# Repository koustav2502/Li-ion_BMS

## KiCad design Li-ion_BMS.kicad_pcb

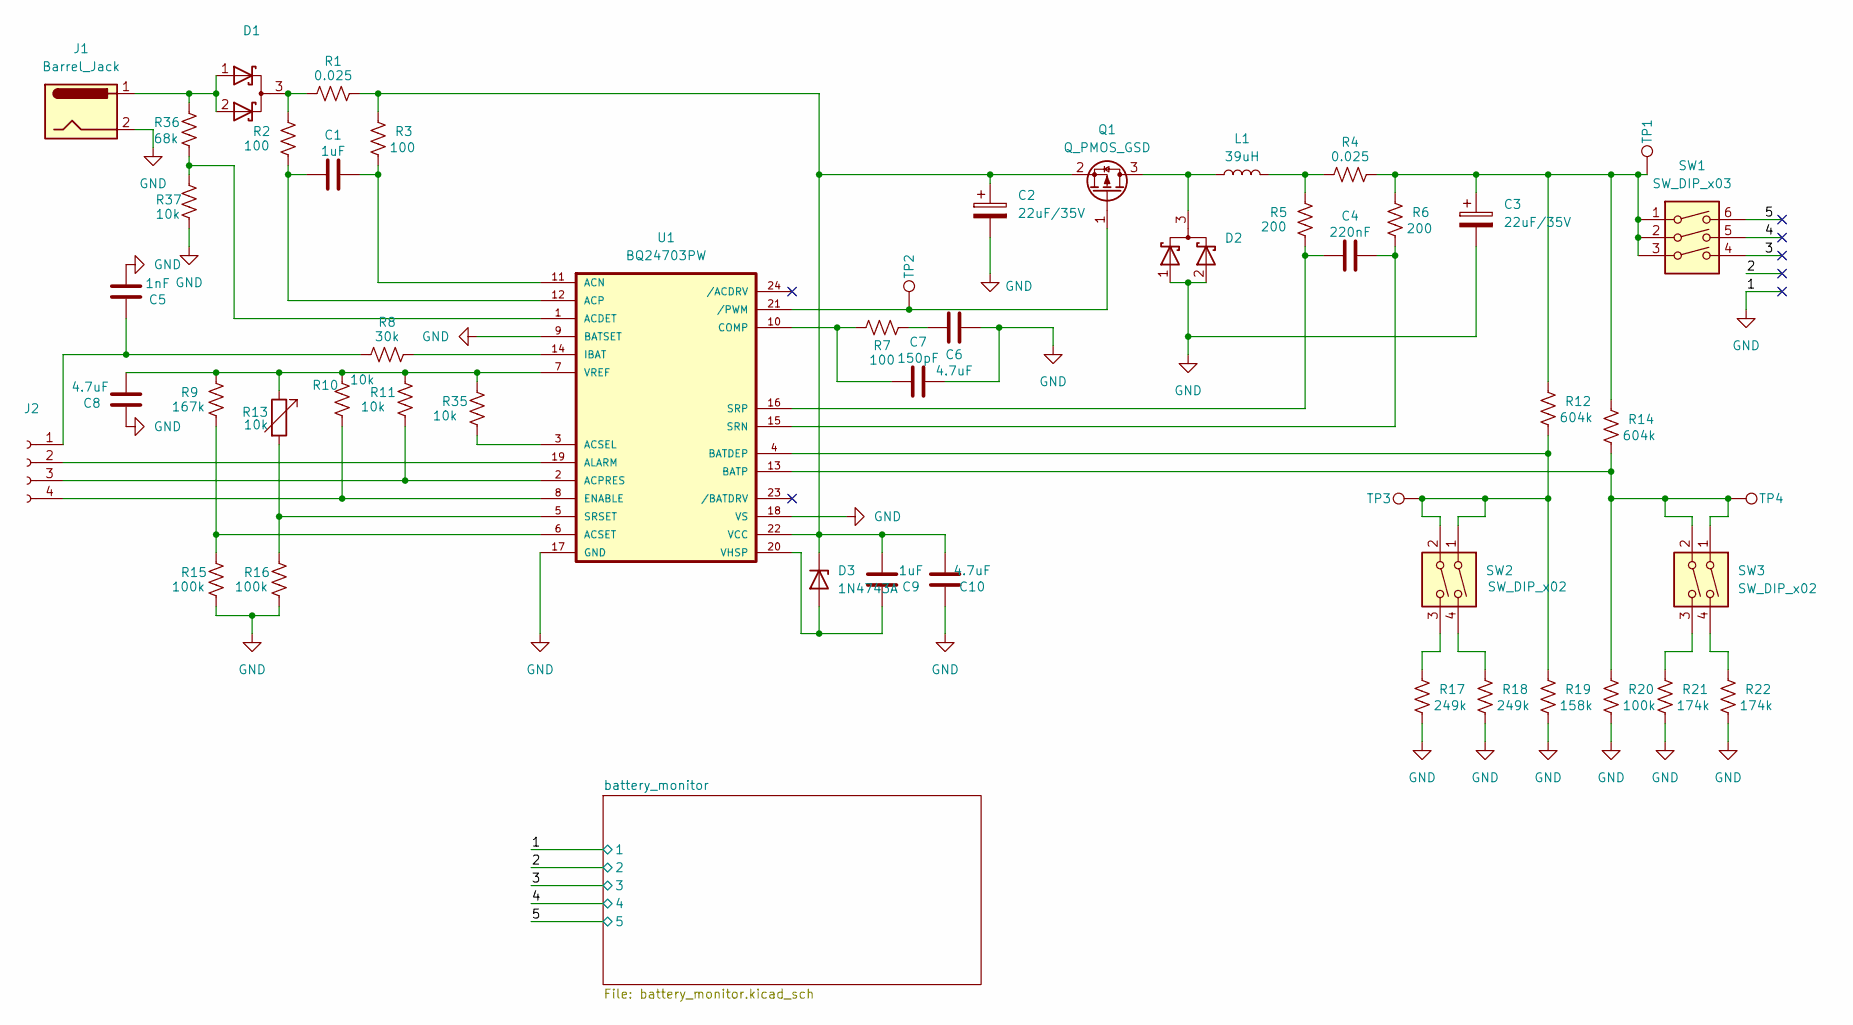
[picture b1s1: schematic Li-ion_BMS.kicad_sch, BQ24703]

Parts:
C1, C9: 1uF; C_Disc_D5.0mm_W2.5mm_P5.00mm
C2, C3: 22uF/35V; CP_Radial_D6.3mm_P2.50mm
C4: 220nF; C_Disc_D5.0mm_W2.5mm_P5.00mm
C5: 1nF; C_Disc_D3.0mm_W1.6mm_P2.50mm
C6, C8, C10: 4.7uF; C_Disc_D5.0mm_W2.5mm_P5.00mm
C7: 150pF; C_Disc_D3.0mm_W1.6mm_P2.50mm
D1, D2: DualSchottkyCommC; TO-220-3_Vertical
D3: 1N4743A; D_DO-41_SOD81_P10.16mm_Horizontal
J1: Barrel_Jack; BarrelJack_Horizontal
J2: Conn_01x04_Socket; PinHeader_1x05_P2.54mm_Vertical
L1: 39uH; L_Radial_D12.0mm_P10.00mm_Neosid_SD12k_style1
Q1: Q_PMOS_GSD; TO-220-3_Vertical
R1, R4: 0.025; R_Axial_DIN0411_L9.9mm_D3.6mm_P15.24mm_Horizontal
R2, R3, R7: 100; R_Axial_DIN0207_L6.3mm_D2.5mm_P10.16mm_Horizontal
R5, R6: 200; R_Axial_DIN0207_L6.3mm_D2.5mm_P10.16mm_Horizontal
R8: 30k; R_Axial_DIN0207_L6.3mm_D2.5mm_P10.16mm_Horizontal
R9: 167k; R_Axial_DIN0207_L6.3mm_D2.5mm_P10.16mm_Horizontal
R10, R11, R35, R37: 10k; R_Axial_DIN0207_L6.3mm_D2.5mm_P10.16mm_Horizontal
R12, R14: 604k; R_Axial_DIN0207_L6.3mm_D2.5mm_P10.16mm_Horizontal
R13: 10k; Potentiometer_Bourns_3296W_Vertical
R15, R16, R20: 100k; R_Axial_DIN0207_L6.3mm_D2.5mm_P10.16mm_Horizontal
R17, R18: 249k; R_Axial_DIN0207_L6.3mm_D2.5mm_P10.16mm_Horizontal
R19: 158k; R_Axial_DIN0207_L6.3mm_D2.5mm_P10.16mm_Horizontal
R21, R22: 174k; R_Axial_DIN0207_L6.3mm_D2.5mm_P10.16mm_Horizontal
R36: 68k; R_Axial_DIN0207_L6.3mm_D2.5mm_P10.16mm_Horizontal
SW1: SW_DIP_x03; SW_DIP_SPSTx03_Slide_9.78x9.8mm_W8.61mm_P2.54mm
SW2, SW3: SW_DIP_x02; SW_DIP_SPSTx02_Slide_9.78x7.26mm_W8.61mm_P2.54mm
TP1, TP2, TP3, TP4: TestPoint; TestPoint_THTPad_D2.0mm_Drill1.0mm
U1: BQ24703PW; TSSOP-24_4.4x7.8mm_P0.65mm

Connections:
/3: SW1.4; also elsewhere on the board
/4: SW1.5; also elsewhere on the board
/5: SW1.6; also elsewhere on the board
GND: C2.2, C3.2, C5.1, C6.2, C7.2, C8.2, C10.2, D2.1 (A), D2.2 (A), J1.2, R15.2, R16.2, R17.2, R18.2, R19.2, R20.2, R21.2, R22.2, R37.2, U1.9 (BATSET), U1.17 (GND), U1.18 (VS); also elsewhere on the board
unnamed: C3.1, R4.1, R6.1, R12.1, R14.1, SW1.1, SW1.2, SW1.3, TP1.1 (1_1)
unnamed: C6.1, R7.1
unnamed: D1.1 (A), D1.2 (A), J1.1, R36.1
unnamed: D1.3 (K), R1.2, R2.1
unnamed: D2.3 (K), L1.1, Q1.3 (D)
unnamed: C9.2, D3.2 (A), U1.20 (VHSP)
unnamed: C2.1, C9.1, C10.1, D3.1 (K), Q1.2 (S), R1.1, R3.1, U1.22 (VCC)
unnamed: C5.2, J2.1, R8.2
unnamed: J2.2, U1.19 (ALARM)
unnamed: J2.3, R11.2, U1.2 (ACPRES)
unnamed: J2.4, R10.2, U1.8 (ENABLE)
unnamed: L1.2, R4.2, R5.1
unnamed: Q1.1 (G), TP2.1 (1_1), U1.21 (/PWM)
unnamed: R17.1, SW2.3
unnamed: R18.1, SW2.4
unnamed: R21.1, SW3.3
unnamed: R22.1, SW3.4
unnamed: R36.2, R37.1, U1.1 (ACDET)
unnamed: C1.2, R3.2, U1.11 (ACN)
unnamed: C1.1, R2.2, U1.12 (ACP)
unnamed: R35.2, U1.3 (ACSEL)
unnamed: R9.2, R15.1, U1.6 (ACSET)
unnamed: R12.2, R19.1, SW2.1, SW2.2, TP3.1 (1_1), U1.4 (BATDEP)
unnamed: R14.2, R20.1, SW3.1, SW3.2, TP4.1 (1_1), U1.13 (BATP)
unnamed: C7.1, R7.2, U1.10 (COMP)
unnamed: R8.1, U1.14 (IBAT)
unnamed: C4.2, R6.2, U1.15 (SRN)
unnamed: C4.1, R5.2, U1.16 (SRP)
unnamed: R13.2, R16.1, U1.5 (SRSET)
unnamed: C8.1, R9.1, R10.1, R11.1, R13.1, R35.1, U1.7 (VREF)

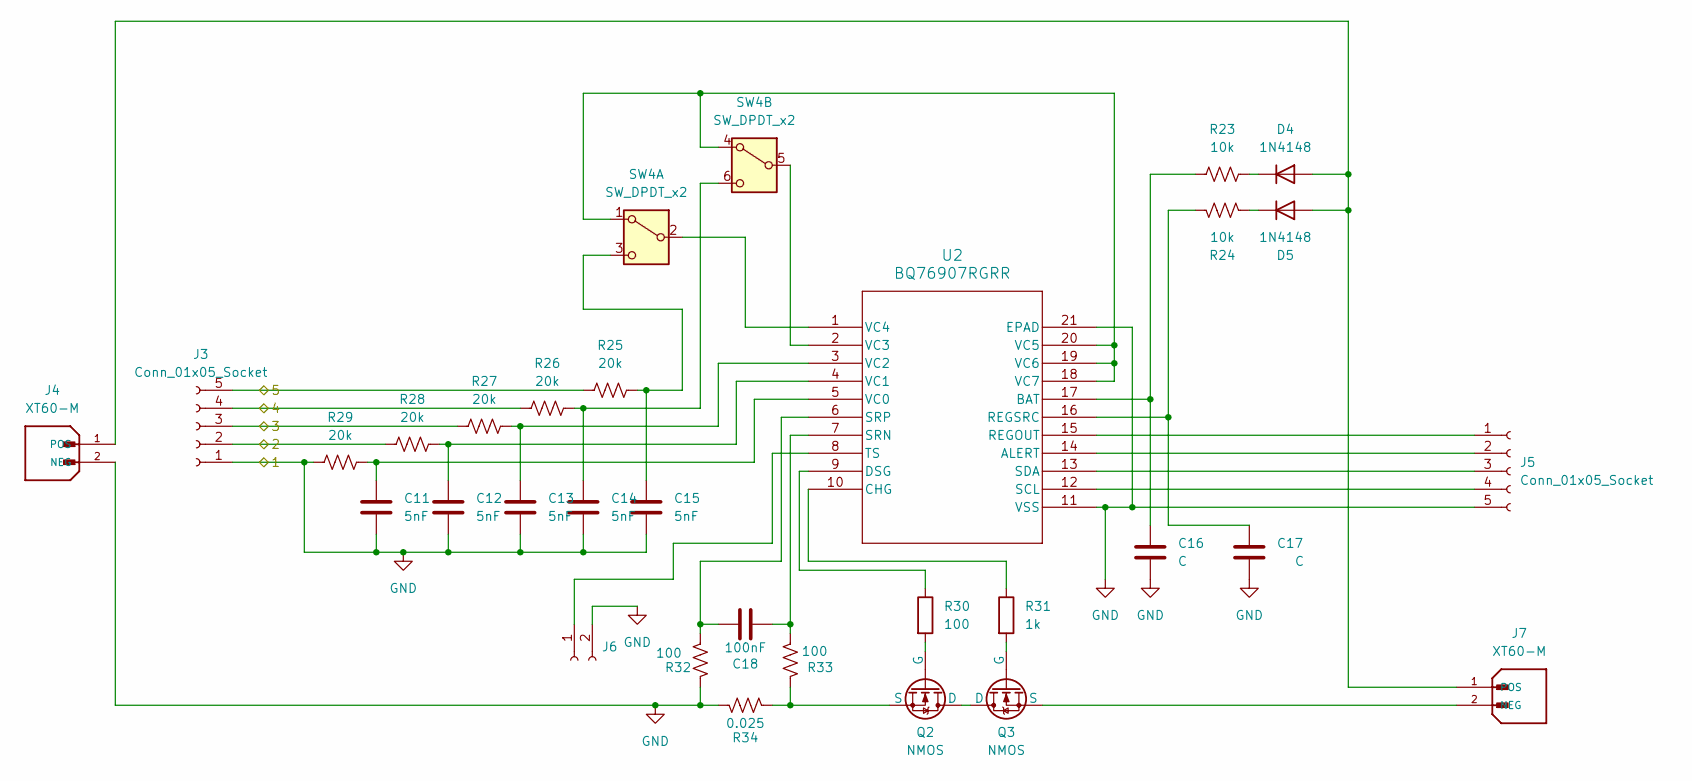
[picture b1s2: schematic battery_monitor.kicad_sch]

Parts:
C11, C12, C13, C14, C15: 5nF; C_Disc_D3.0mm_W1.6mm_P2.50mm
C16, C17: C; C_Disc_D5.0mm_W2.5mm_P5.00mm
C18: 100nF; C_Disc_D5.0mm_W2.5mm_P5.00mm
D4, D5: 1N4148; D_DO-35_SOD27_P7.62mm_Horizontal
J3: Conn_01x05_Socket; JST_XH_B5B-XH-A_1x05_P2.50mm_Vertical
J4, J7: XT60-M; AMASS_XT60-M_1x02_P7.20mm_Vertical; PARTREV V1.2
J5: Conn_01x05_Socket; PinHeader_1x05_P2.54mm_Vertical
J6: Conn_01x02_Socket; JST_XH_B2B-XH-A_1x02_P2.50mm_Vertical
Q2, Q3: NMOS; TO-220-3_Vertical
R23, R24: 10k; R_Axial_DIN0207_L6.3mm_D2.5mm_P10.16mm_Horizontal
R25, R26, R27, R28, R29: 20k; R_Axial_DIN0207_L6.3mm_D2.5mm_P10.16mm_Horizontal
R30, R32, R33: 100; R_Axial_DIN0207_L6.3mm_D2.5mm_P10.16mm_Horizontal
R31: 1k; R_Axial_DIN0207_L6.3mm_D2.5mm_P10.16mm_Horizontal
R34: 0.025; R_Axial_DIN0614_L14.3mm_D5.7mm_P20.32mm_Horizontal
SW4: SW_DPDT_x2; SW_DIP_SPSTx03_Slide_9.78x9.8mm_W8.61mm_P2.54mm
U2: BQ76907RGRR; QFN-20-1EP_3.5x3.5mm_P0.5mm_EP2x2mm

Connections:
/2: J3.2, R28.2
/3: J3.3, R27.2; also elsewhere on the board
/4: J3.4, R26.2; also elsewhere on the board
/5: J3.5, R25.2; also elsewhere on the board
GND: C11.2, C12.2, C13.2, C14.2, C15.2, C16.2, C17.2, J3.1, J4.2 (NEG), J5.5, J6.2, R29.2, R32.1, R34.2, U2.11 (VSS), U2.21 (EPAD); also elsewhere on the board
unnamed: D4.2 (A), D5.2 (A), J4.1 (POS), J7.1 (POS)
unnamed: D4.1 (K), R23.1
unnamed: D5.1 (K), R24.1
unnamed: J5.1, U2.15 (REGOUT)
unnamed: J5.2, U2.14 (ALERT)
unnamed: J5.3, U2.13 (SDA)
unnamed: J5.4, U2.12 (SCL)
unnamed: J6.1, U2.8 (TS)
unnamed: J7.2 (NEG), Q3.3 (S)
unnamed: Q2.1 (D), Q3.1 (D)
unnamed: Q2.2 (G), R30.2
unnamed: Q2.3 (S), R33.1, R34.1
unnamed: Q3.2 (G), R31.2
unnamed: SW4.1 (A), SW4.4 (A), U2.18 (VC7), U2.19 (VC6), U2.20 (VC5)
unnamed: SW4.2 (B), U2.1 (VC4)
unnamed: C15.1, R25.1, SW4.3 (C)
unnamed: SW4.5 (B), U2.2 (VC3)
unnamed: C14.1, R26.1, SW4.6 (C)
unnamed: C16.1, R23.2, U2.17 (BAT)
unnamed: R31.1, U2.10 (CHG)
unnamed: R30.1, U2.9 (DSG)
unnamed: C17.1, R24.2, U2.16 (REGSRC)
unnamed: C18.2, R33.2, U2.7 (SRN)
unnamed: C18.1, R32.2, U2.6 (SRP)
unnamed: C11.1, R29.1, U2.5 (VC0)
unnamed: C12.1, R28.1, U2.4 (VC1)
unnamed: C13.1, R27.1, U2.3 (VC2)

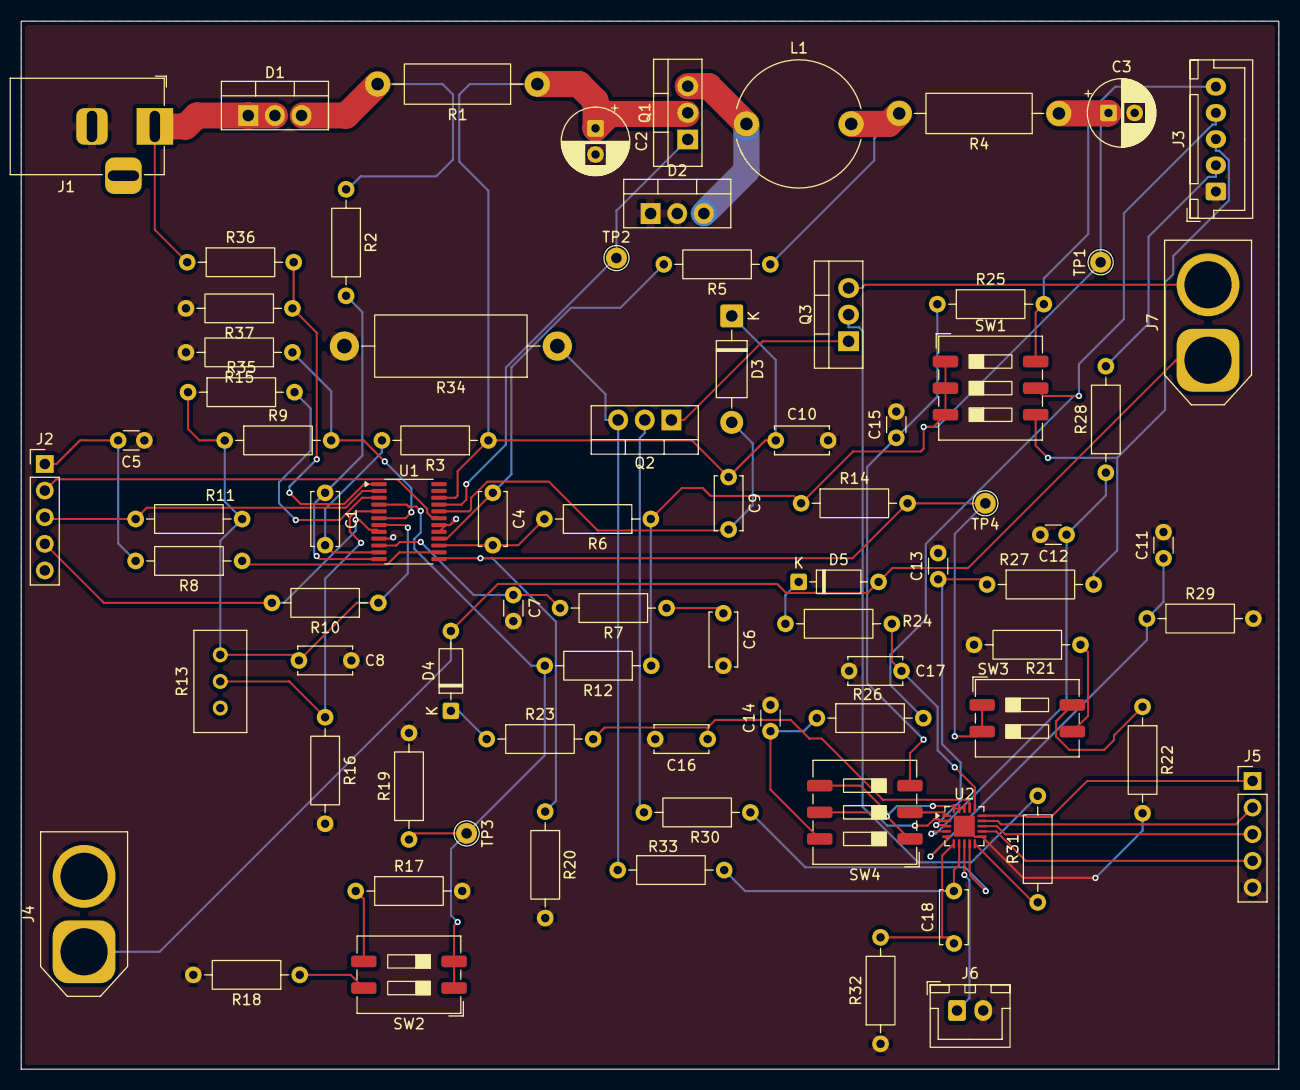
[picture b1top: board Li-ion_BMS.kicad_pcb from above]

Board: 2 copper layers, 120.0 x 100.0 mm, 81 parts (0 on the bottom side), 62 nets.
